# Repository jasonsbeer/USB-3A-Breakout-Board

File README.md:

# USB 3 Type A Breakout Board

I needed a USB breakout for some prototyping work and could not find one. So, I made one. Feel free to use it if you need one. There are two connections for VBUS and GND to provide options for power connection.

This accepts a USB 3.x type A style socket, such as Digikey part number 2057-USB-A3-S-RA-ND.

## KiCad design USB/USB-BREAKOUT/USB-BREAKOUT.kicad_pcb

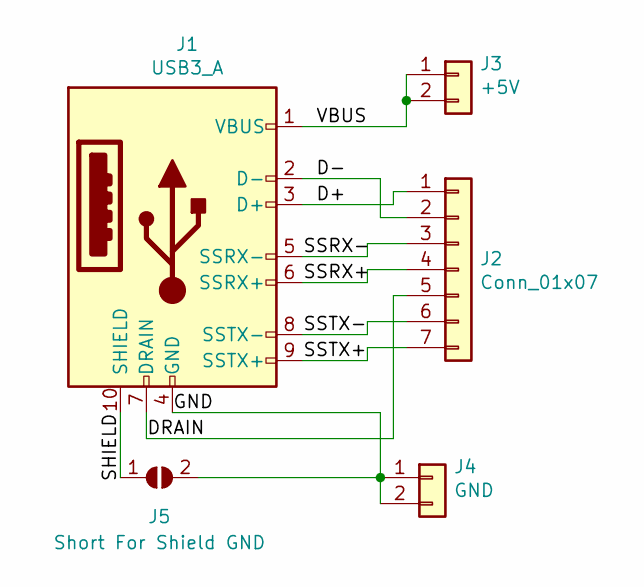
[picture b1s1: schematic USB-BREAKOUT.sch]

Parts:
J1: USB3_A; USB3_A_AdamTech
J2: Conn_01x07; PinHeader_1x07_P2.54mm_Vertical
J3: +5V; PinHeader_1x02_P2.54mm_Vertical
J4: GND; PinHeader_1x02_P2.54mm_Vertical
J5: Short For Shield GND; SolderJumper-2_P1.3mm_Open_RoundedPad1.0x1.5mm

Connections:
/D+: J1.3 (D+), J2.1
/D-: J1.2 (D-), J2.2
/DRAIN: J1.7 (DRAIN), J2.5
/GND: J1.4 (GND), J4.1, J4.2, J5.2 (B)
/SHIELD: J1.10 (SHIELD), J5.1 (A)
/SSRX+: J1.6 (SSRX+), J2.4
/SSRX-: J1.5 (SSRX-), J2.3
/SSTX+: J1.9 (SSTX+), J2.7
/SSTX-: J1.8 (SSTX-), J2.6
/VBUS: J1.1 (VBUS), J3.1, J3.2

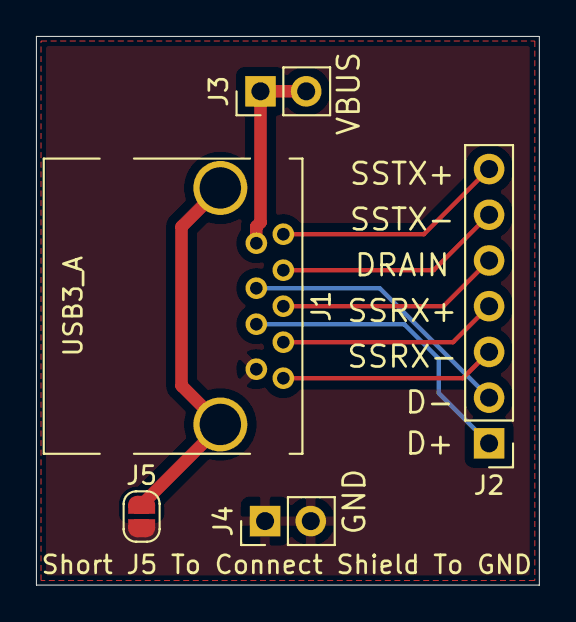
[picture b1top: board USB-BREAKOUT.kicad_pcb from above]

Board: 2 copper layers, 27.9 x 30.5 mm, 5 parts (0 on the bottom side), 10 nets.
